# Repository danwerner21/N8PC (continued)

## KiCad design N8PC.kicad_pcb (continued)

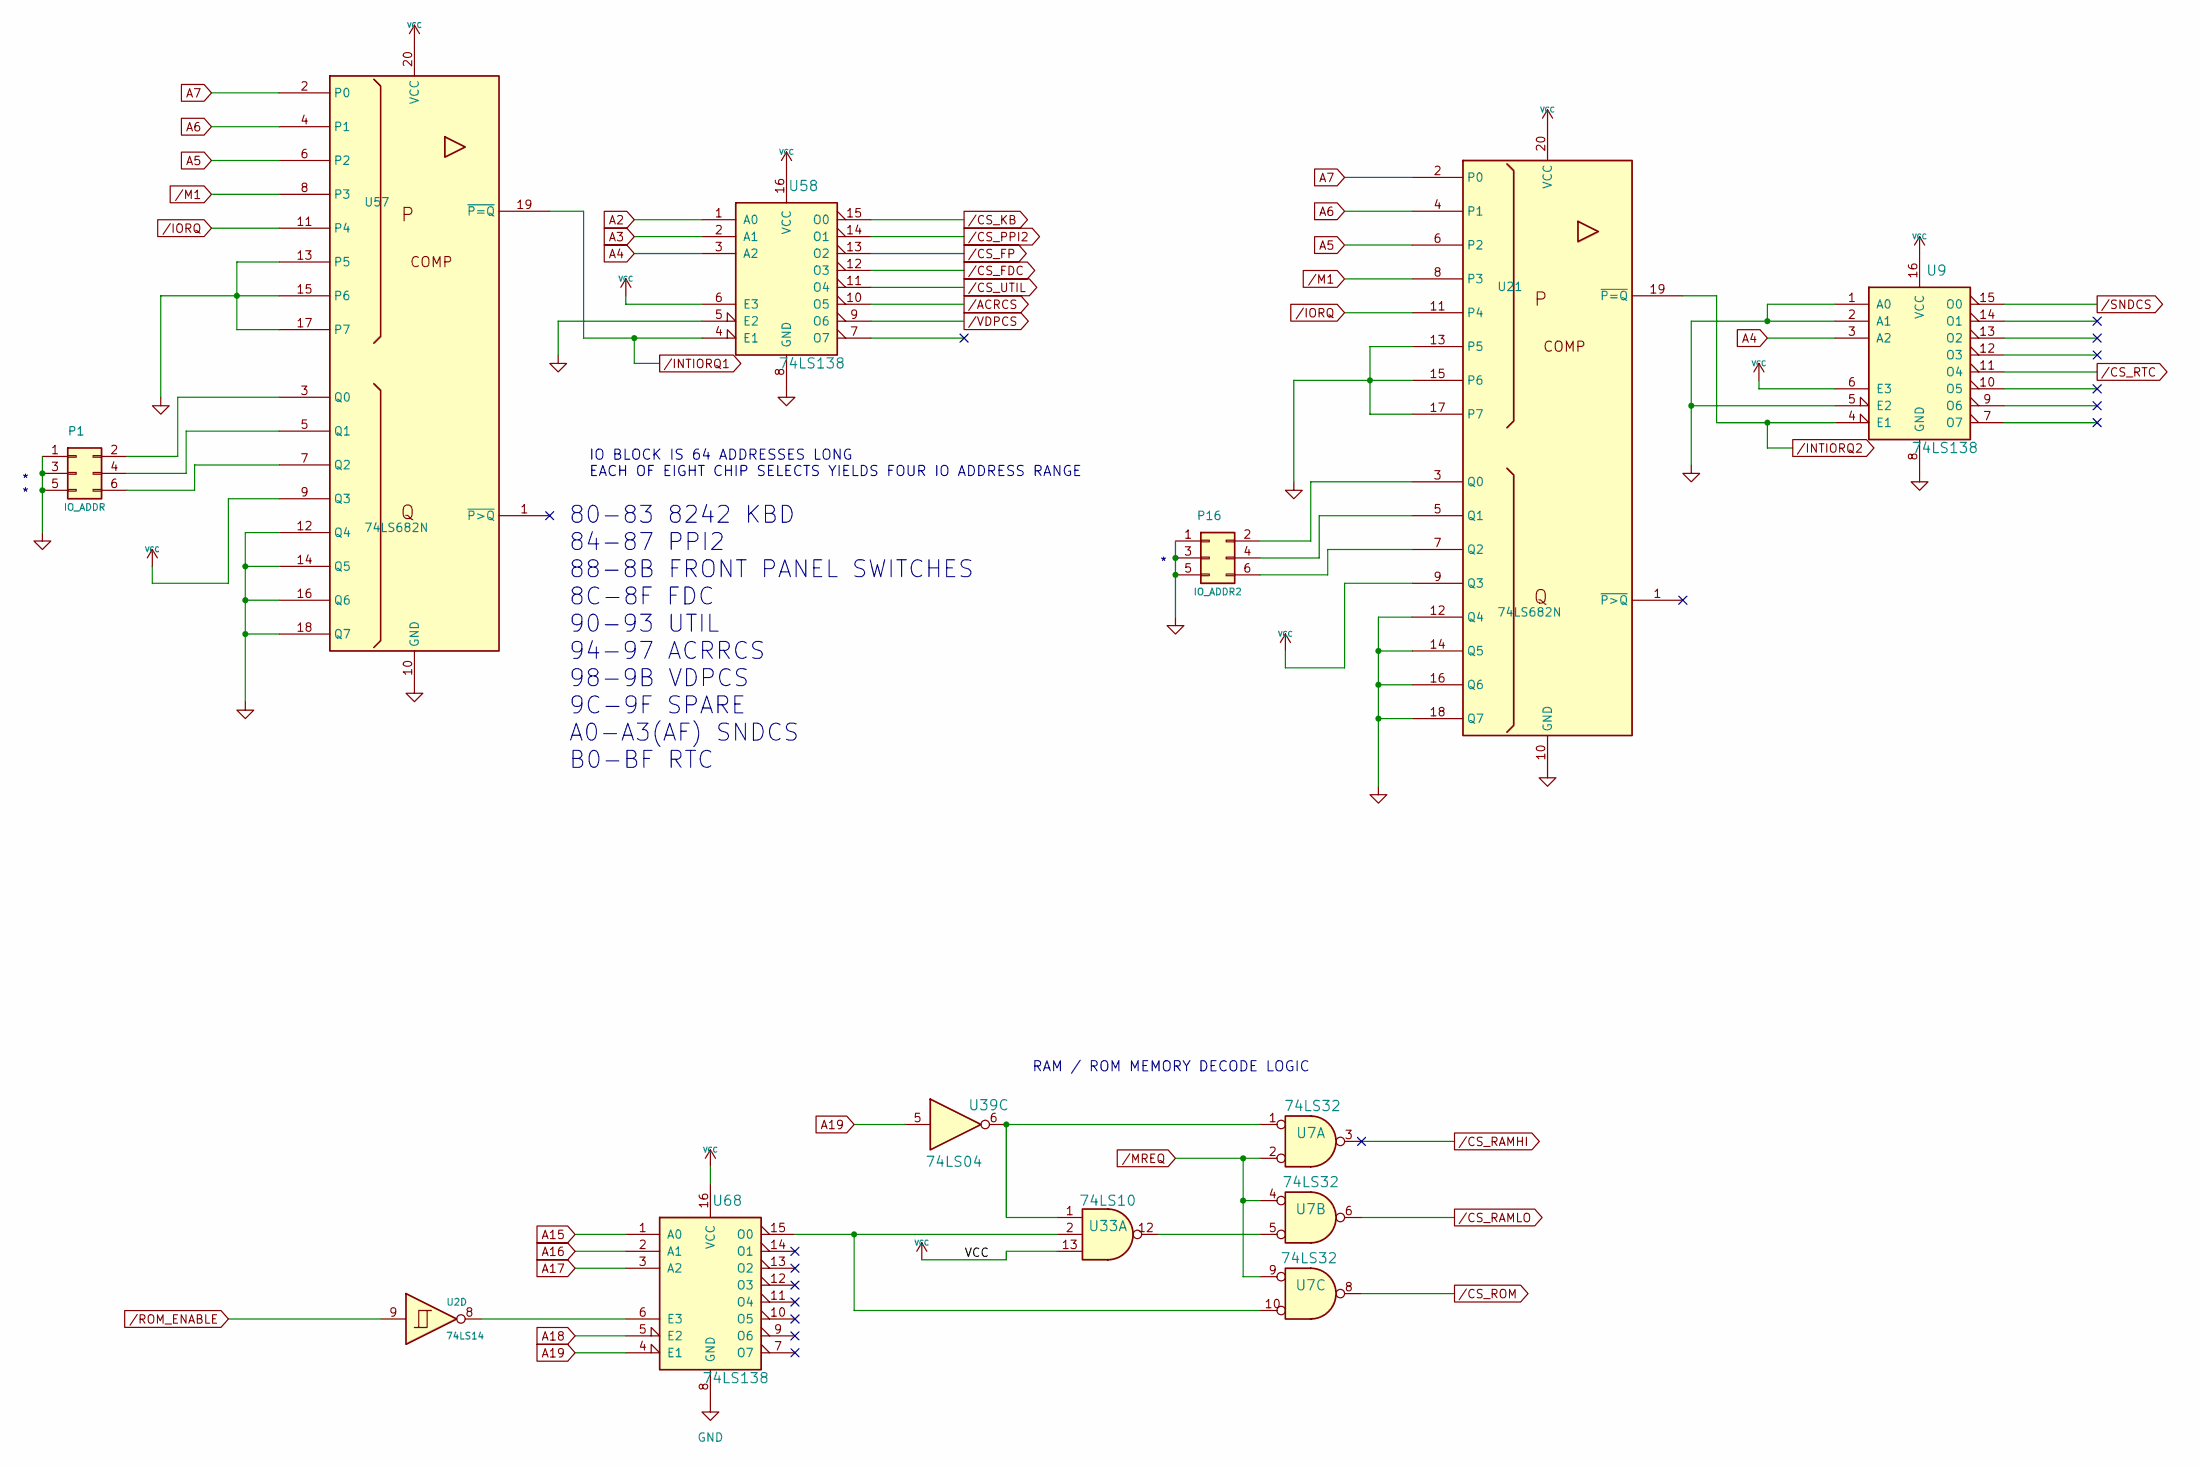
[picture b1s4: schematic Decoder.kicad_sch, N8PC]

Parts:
P1: IO_ADDR; STD_DDW_PinHeader_2x03
P16: IO_ADDR2; STD_DDW_PinHeader_2x03
U2: 74LS14; STD_DDW_DIP14
U7: 74LS32; STD_DDW_DIP14
U9, U58, U68: 74LS138; STD_DDW_DIP16
U21, U57: 74LS682N; STD_DDW_DIP20
U33: 74LS10; STD_DDW_DIP14
U39: 74LS04; STD_DDW_DIP14

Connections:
+5V: U9.6 (E3), U9.16 (VCC), U21.9 (Q3), U21.20 (VCC), U33.13, U57.9 (Q3), U57.20 (VCC), U58.6 (E3), U58.16 (VCC), U68.16 (VCC); also elsewhere on the board
A2: U58.1 (A0); also elsewhere on the board
A3: U58.2 (A1); also elsewhere on the board
A4: U9.3 (A2), U58.3 (A2); also elsewhere on the board
A5: U21.6 (P2), U57.6 (P2); also elsewhere on the board
A6: U21.4 (P1), U57.4 (P1); also elsewhere on the board
A7: U21.2 (P0), U57.2 (P0); also elsewhere on the board
A15: U68.1 (A0); also elsewhere on the board
A16: U68.2 (A1); also elsewhere on the board
A17: U68.3 (A2); also elsewhere on the board
A18: U68.5 (E2); also elsewhere on the board
A19: U39.5, U68.4 (E1); also elsewhere on the board
GND: P1.1, P1.3, P1.5, P16.1, P16.3, P16.5, U9.1 (A0), U9.2 (A1), U9.5 (E2), U9.8 (GND), U21.10 (GND), U21.12 (Q4), U21.13 (P5), U21.14 (Q5), U21.15 (P6), U21.16 (Q6), U21.17 (P7), U21.18 (Q7), U57.10 (GND), U57.12 (Q4), U57.13 (P5), U57.14 (Q5), U57.15 (P6), U57.16 (Q6), U57.17 (P7), U57.18 (Q7), U58.5 (E2), U58.8 (GND), U68.8 (GND); also elsewhere on the board
unnamed: P1.2, U57.3 (Q0)
unnamed: P1.4, U57.5 (Q1)
unnamed: P1.6, U57.7 (Q2)
unnamed: P16.2, U21.3 (Q0)
unnamed: P16.4, U21.5 (Q1)
unnamed: P16.6, U21.7 (Q2)
unnamed: U7.1, U33.1, U39.6
unnamed: U7.5, U33.12
unnamed: U2.8, U68.6 (E3)
unnamed: U7.10, U33.2, U68.15 (O0)
/ACRCS: U58.10 (O5); also elsewhere on the board
/CS_FDC: U58.12 (O3); also elsewhere on the board
/CS_FP: U58.13 (O2); also elsewhere on the board
/CS_KB: U58.15 (O0); also elsewhere on the board
/CS_PPI2: U58.14 (O1); also elsewhere on the board
/CS_RAMHI: U7.3
/CS_RAMLO: U7.6; also elsewhere on the board
/CS_ROM: U7.8; also elsewhere on the board
/CS_RTC: U9.11 (O4); also elsewhere on the board
/CS_UTIL: U58.11 (O4); also elsewhere on the board
/INTIORQ1: U57.19 (~P=Q), U58.4 (E1); also elsewhere on the board
/INTIORQ2: U9.4 (E1), U21.19 (~P=Q); also elsewhere on the board
/IORQ: U21.11 (P4), U57.11 (P4); also elsewhere on the board
/M1: U21.8 (P3), U57.8 (P3); also elsewhere on the board
/MREQ: U7.2, U7.4, U7.9; also elsewhere on the board
/ROM_ENABLE: U2.9; also elsewhere on the board
/SNDCS: U9.15 (O0); also elsewhere on the board
/VDPCS: U58.9 (O6); also elsewhere on the board

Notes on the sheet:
* *
RAM / ROM MEMORY DECODE LOGIC
80-83 8242 KBD 84-87 PPI2 88-8B FRONT PANEL SWITCHES 8C-8F FDC 90-93 UTIL 94-97 ACRRCS 98-9B VDPCS 9C-9F SPARE A0-A3(AF) SNDCS B0-BF RTC
IO BLOCK IS 64 ADDRESSES LONG EACH OF EIGHT CHIP SELECTS YIELDS FOUR IO ADDRESS RANGE

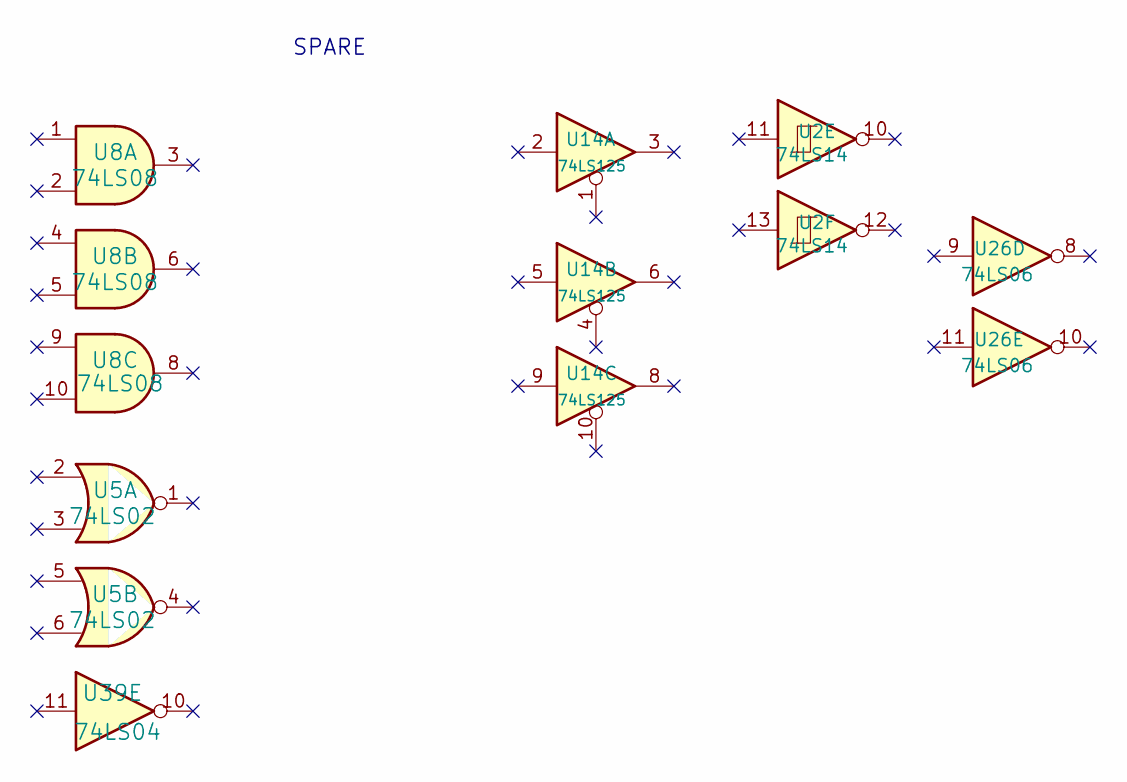
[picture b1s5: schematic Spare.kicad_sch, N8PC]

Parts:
U2: 74LS14; STD_DDW_DIP14
U5: 74LS02; STD_DDW_DIP14
U8: 74LS08; STD_DDW_DIP14
U14: 74LS125; STD_DDW_DIP14
U26: 74LS06; STD_DDW_DIP14
U39: 74LS04; STD_DDW_DIP14

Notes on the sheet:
SPARE

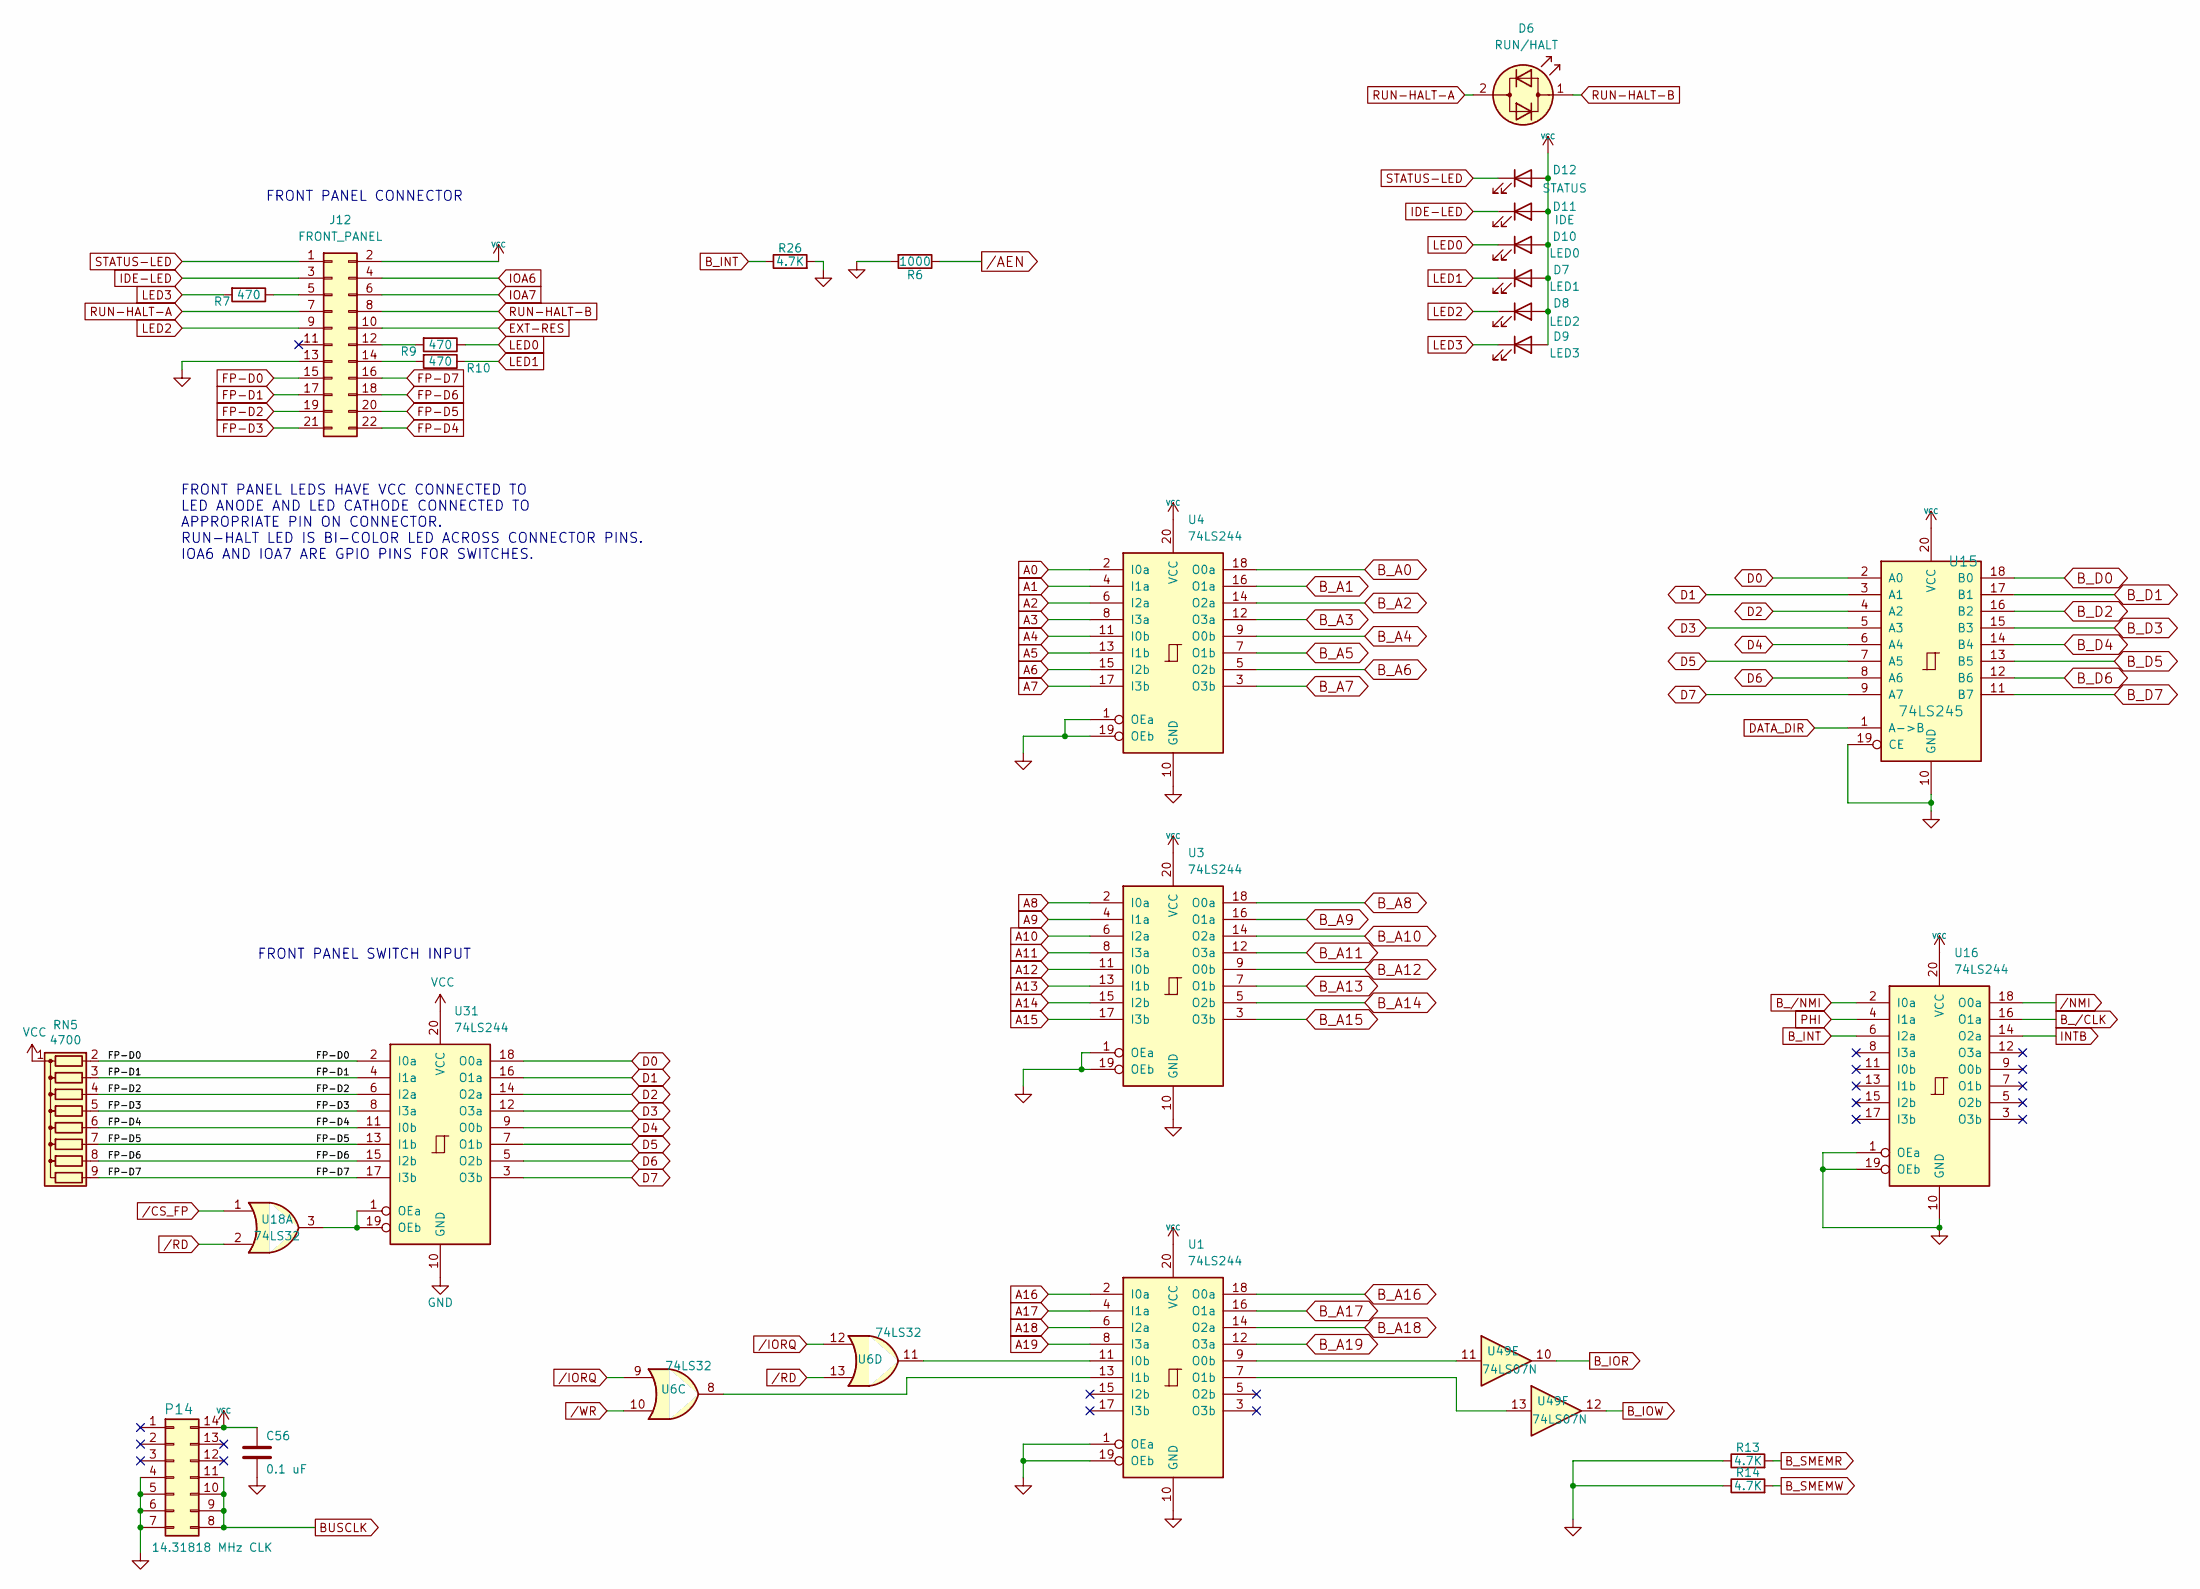
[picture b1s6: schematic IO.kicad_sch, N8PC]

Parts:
C56: 0.1 uF; STD_DDW_CAP
D6: RUN/HALT; STD_DDW_LED5
D7: LED1; STD_DDW_LED5
D8: LED2; STD_DDW_LED5
D9: LED3; STD_DDW_LED5
D10: LED0; STD_DDW_LED5
D11: IDE; STD_DDW_LED5
D12: STATUS; STD_DDW_LED5
J12: FRONT_PANEL; STD_DDW_PinHeader_2x11
P14: 14.31818 MHz CLK; STD_DDW_DIP14
R6: 1000; STD_DDW_RESISTOR
R7, R9, R10: 470; STD_DDW_RESISTOR
R13, R14, R26: 4.7K; STD_DDW_RESISTOR
RN5: 4700; R_Array_SIP9
U1, U3, U4, U16, U31: 74LS244; STD_DDW_DIP20
U6, U18: 74LS32; STD_DDW_DIP14
U15: 74LS245; STD_DDW_DIP20
U49: 74LS07N; STD_DDW_DIP14

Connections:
+5V: C56.1, D7.2 (A), D8.2 (A), D9.2 (A), D10.2 (A), D11.2 (A), D12.2 (A), J12.2, P14.14, RN5.1 (common), U1.20 (VCC), U3.20 (VCC), U4.20 (VCC), U15.20 (VCC), U16.20 (VCC), U31.20 (VCC); also elsewhere on the board
A0: U4.2 (I0a); also elsewhere on the board
A1: U4.4 (I1a); also elsewhere on the board
A2: U4.6 (I2a); also elsewhere on the board
A3: U4.8 (I3a); also elsewhere on the board
A4: U4.11 (I0b); also elsewhere on the board
A5: U4.13 (I1b); also elsewhere on the board
A6: U4.15 (I2b); also elsewhere on the board
A7: U4.17 (I3b); also elsewhere on the board
A8: U3.2 (I0a); also elsewhere on the board
A9: U3.4 (I1a); also elsewhere on the board
A10: U3.6 (I2a); also elsewhere on the board
A11: U3.8 (I3a); also elsewhere on the board
A12: U3.11 (I0b); also elsewhere on the board
A13: U3.13 (I1b); also elsewhere on the board
A14: U3.15 (I2b); also elsewhere on the board
A15: U3.17 (I3b); also elsewhere on the board
A16: U1.2 (I0a); also elsewhere on the board
A17: U1.4 (I1a); also elsewhere on the board
A18: U1.6 (I2a); also elsewhere on the board
A19: U1.8 (I3a); also elsewhere on the board
BUSCLK: P14.8, P14.9, P14.10, P14.11; also elsewhere on the board
B_A0: U4.18 (O0a); also elsewhere on the board
B_A1: U4.16 (O1a); also elsewhere on the board
B_A2: U4.14 (O2a); also elsewhere on the board
B_A3: U4.12 (O3a); also elsewhere on the board
B_A4: U4.9 (O0b); also elsewhere on the board
B_A5: U4.7 (O1b); also elsewhere on the board
B_A6: U4.5 (O2b); also elsewhere on the board
B_A7: U4.3 (O3b); also elsewhere on the board
B_A8: U3.18 (O0a); also elsewhere on the board
B_A9: U3.16 (O1a); also elsewhere on the board
B_A10: U3.14 (O2a); also elsewhere on the board
B_A11: U3.12 (O3a); also elsewhere on the board
B_A12: U3.9 (O0b); also elsewhere on the board
B_A13: U3.7 (O1b); also elsewhere on the board
B_A14: U3.5 (O2b); also elsewhere on the board
B_A15: U3.3 (O3b); also elsewhere on the board
B_A16: U1.18 (O0a); also elsewhere on the board
B_A17: U1.16 (O1a); also elsewhere on the board
B_A18: U1.14 (O2a); also elsewhere on the board
B_A19: U1.12 (O3a); also elsewhere on the board
B_D0: U15.18 (B0); also elsewhere on the board
B_D1: U15.17 (B1); also elsewhere on the board
B_D2: U15.16 (B2); also elsewhere on the board
B_D3: U15.15 (B3); also elsewhere on the board
B_D4: U15.14 (B4); also elsewhere on the board
B_D5: U15.13 (B5); also elsewhere on the board
B_D6: U15.12 (B6); also elsewhere on the board
B_D7: U15.11 (B7); also elsewhere on the board
B_INT: R26.1, U16.6 (I2a); also elsewhere on the board
B_IOR: U49.10; also elsewhere on the board
B_IOW: U49.12; also elsewhere on the board
B_SMEMR: R13.2; also elsewhere on the board
B_SMEMW: R14.2; also elsewhere on the board
B_/CLK: U16.16 (O1a); also elsewhere on the board
B_/NMI: U16.2 (I0a); also elsewhere on the board
D0: U15.2 (A0), U31.18 (O0a); also elsewhere on the board
D1: U15.3 (A1), U31.16 (O1a); also elsewhere on the board
D2: U15.4 (A2), U31.14 (O2a); also elsewhere on the board
D3: U15.5 (A3), U31.12 (O3a); also elsewhere on the board
D4: U15.6 (A4), U31.9 (O0b); also elsewhere on the board
D5: U15.7 (A5), U31.7 (O1b); also elsewhere on the board
D6: U15.8 (A6), U31.5 (O2b); also elsewhere on the board
D7: U15.9 (A7), U31.3 (O3b); also elsewhere on the board
DATA_DIR: U15.1 (A->B); also elsewhere on the board
EXT-RES: J12.10; also elsewhere on the board
FP-D0: J12.15, RN5.2 (R1), U31.2 (I0a)
FP-D1: J12.17, RN5.3 (R2), U31.4 (I1a)
FP-D2: J12.19, RN5.4 (R3), U31.6 (I2a)
FP-D3: J12.21, RN5.5 (R4), U31.8 (I3a)
FP-D4: J12.22, RN5.6 (R5), U31.11 (I0b)
FP-D5: J12.20, RN5.7 (R6), U31.13 (I1b)
FP-D6: J12.18, RN5.8 (R7), U31.15 (I2b)
FP-D7: J12.16, RN5.9 (R8), U31.17 (I3b)
GND: C56.2, J12.13, P14.4, P14.5, P14.6, P14.7, R6.2, R13.1, R14.1, R26.2, U1.1 (OEa), U1.10 (GND), U1.19 (OEb), U3.1 (OEa), U3.10 (GND), U3.19 (OEb), U4.1 (OEa), U4.10 (GND), U4.19 (OEb), U15.10 (GND), U15.19 (CE), U16.1 (OEa), U16.10 (GND), U16.19 (OEb), U31.10 (GND); also elsewhere on the board
IDE-LED: D11.1 (K), J12.3; also elsewhere on the board
INTB: U16.14 (O2a); also elsewhere on the board
IOA6: J12.4; also elsewhere on the board
IOA7: J12.6; also elsewhere on the board
LED0: D10.1 (K), R9.1; also elsewhere on the board
LED1: D7.1 (K), R10.1; also elsewhere on the board
LED2: D8.1 (K), J12.9; also elsewhere on the board
LED3: D9.1 (K), R7.2; also elsewhere on the board
unnamed: J12.5, R7.1
unnamed: J12.12, R9.2
unnamed: J12.14, R10.2
unnamed: U1.11 (I0b), U6.11
unnamed: U1.13 (I1b), U6.8
unnamed: U1.9 (O0b), U49.11
unnamed: U1.7 (O1b), U49.13
unnamed: U18.3, U31.1 (OEa), U31.19 (OEb)
PHI: U16.4 (I1a); also elsewhere on the board
RUN-HALT-A: D6.2 (AK), J12.7; also elsewhere on the board
RUN-HALT-B: D6.1 (KA), J12.8; also elsewhere on the board
STATUS-LED: D12.1 (K), J12.1; also elsewhere on the board
/AEN: R6.1; also elsewhere on the board
/CS_FP: U18.1; also elsewhere on the board
/IORQ: U6.9, U6.12; also elsewhere on the board
/NMI: U16.18 (O0a); also elsewhere on the board
/RD: U6.13, U18.2; also elsewhere on the board
/WR: U6.10; also elsewhere on the board

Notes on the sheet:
FRONT PANEL CONNECTOR
FRONT PANEL LEDS HAVE VCC CONNECTED TO LED ANODE AND LED CATHODE CONNECTED TO APPROPRIATE PIN ON CONNECTOR. RUN-HALT LED IS BI-COLOR LED ACROSS CONNECTOR PINS. IOA6 AND IOA7 ARE GPIO PINS FOR SWITCHES.
FRONT PANEL SWITCH INPUT

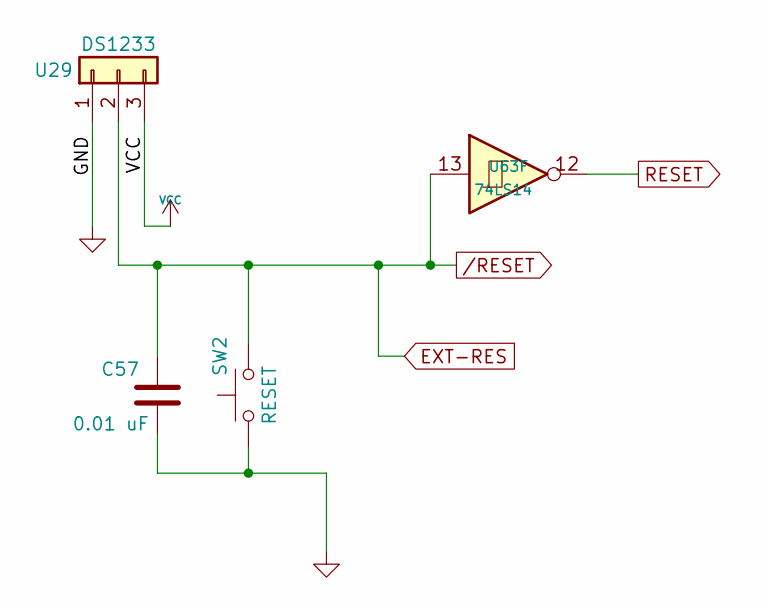
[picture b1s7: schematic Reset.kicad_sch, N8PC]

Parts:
C57: 0.01 uF; STD_DDW_CAP
SW2: RESET; STD_DDW_TACTSW
U29: DS1233; STD_DDW_TO92
U63: 74LS14; STD_DDW_DIP14

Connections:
+5V: U29.3; also elsewhere on the board
EXT-RES: C57.1, SW2.2, U29.2, U63.13; also elsewhere on the board
GND: C57.2, SW2.1, U29.1; also elsewhere on the board
RESET: U63.12; also elsewhere on the board

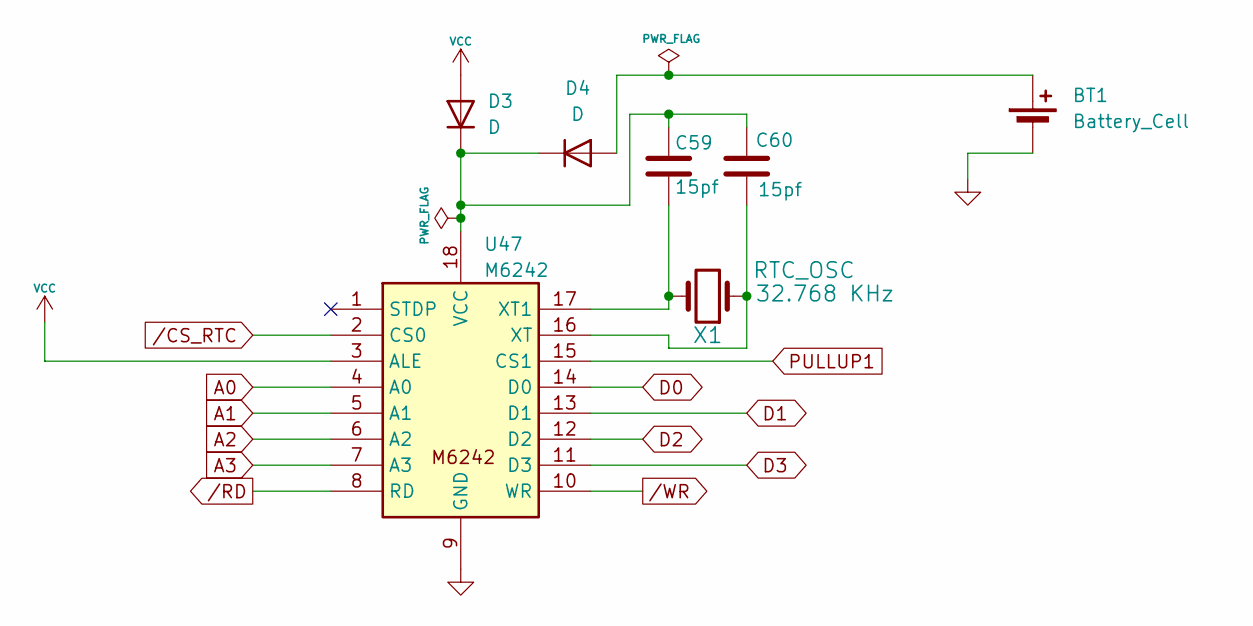
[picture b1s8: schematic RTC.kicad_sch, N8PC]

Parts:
BT1: Battery_Cell; BatteryHolder_MYOUNG_BS-07-A1BJ001_CR2032
C59, C60: 15pf; STD_DDW_CAP
D3, D4: D; STD_DDW_DIODE
U47: M6242; STD_DDW_DIP18
X1: RTC_OSC; DDW_STD_RTCCRYSTAL

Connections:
+5V: D3.2 (A), U47.3 (ALE); also elsewhere on the board
A0: U47.4 (A0); also elsewhere on the board
A1: U47.5 (A1); also elsewhere on the board
A2: U47.6 (A2); also elsewhere on the board
A3: U47.7 (A3); also elsewhere on the board
D0: U47.14 (D0); also elsewhere on the board
D1: U47.13 (D1); also elsewhere on the board
D2: U47.12 (D2); also elsewhere on the board
D3: U47.11 (D3); also elsewhere on the board
GND: BT1.2 (-), U47.9 (GND); also elsewhere on the board
unnamed: BT1.1 (+), D4.2 (A)
unnamed: C59.1, C60.1, D3.1 (K), D4.1 (K), U47.18 (VCC)
unnamed: C59.2, U47.17 (XT1), X1.2
unnamed: C60.2, U47.16 (XT), X1.1
PULLUP1: U47.15 (CS1); also elsewhere on the board
/CS_RTC: U47.2 (CS0); also elsewhere on the board
/RD: U47.8 (RD); also elsewhere on the board
/WR: U47.10 (WR); also elsewhere on the board

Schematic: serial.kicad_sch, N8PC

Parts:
C55, C58, C61, C62, C63, C64, C67, C71, C72, C73: 1.0 uF; STD_DDW_PCAP
J17, J19: TTL SERIAL CONSOLE; STD_DDW_PINHEAD_V_1x06
J18, J20: TTL CONSOLE PWR; STD_DDW_PINHEAD_V_1x02
JP2: CTS0; STD_DDW_PINHEAD_V_1x02
JP3: CTS1; STD_DDW_PINHEAD_V_1x02
P13, P18: SERIAL; STD_DDW_PINHEAD_V_2x05
R4: 4.7K; STD_DDW_RESISTOR
U10, U35: MAX232; STD_DDW_DIP16

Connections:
+5V: C61.1, C63.2, C71.2, C72.1, J18.1, J20.1, R4.1, U10.16 (VCC), U35.16 (VCC); also elsewhere on the board
CTS0: JP2.2 (B), P18.6, U35.13 (R1IN)
CTS1: JP3.2 (B), P13.6, U10.13 (R1IN)
CTS_TTL0: J17.6, U35.12 (R1OUT); also elsewhere on the board
CTS_TTL1: J19.6, U10.12 (R1OUT); also elsewhere on the board
GND: C61.2, C64.1, C72.2, C73.1, J17.1, J19.1, P13.9, P18.9, U10.15 (GND), U35.15 (GND); also elsewhere on the board
unnamed: J17.3, J18.2
unnamed: J19.3, J20.2
unnamed: JP2.1 (A), JP3.1 (A), R4.2
unnamed: C58.1, U10.1 (C1+)
unnamed: C58.2, U10.3 (C1-)
unnamed: C62.1, U10.4 (C2+)
unnamed: C62.2, U10.5 (C2-)
unnamed: C63.1, U10.2 (VS+)
unnamed: C64.2, U10.6 (VS-)
unnamed: C55.1, U35.1 (C1+)
unnamed: C55.2, U35.3 (C1-)
unnamed: C67.1, U35.4 (C2+)
unnamed: C67.2, U35.5 (C2-)
unnamed: C71.1, U35.2 (VS+)
unnamed: C73.2, U35.6 (VS-)
RTS0: P18.4, U35.14 (T1OUT)
RTS1: P13.4, U10.14 (T1OUT)
RTS_TTL0: J17.2, U35.11 (T1IN); also elsewhere on the board
RTS_TTL1: J19.2, U10.11 (T1IN); also elsewhere on the board
RX0: P18.3, U35.8 (R2IN)
RX1: P13.3, U10.8 (R2IN)
SIN_TTL0: J17.4, U35.9 (R2OUT); also elsewhere on the board
SIN_TTL1: J19.4, U10.9 (R2OUT); also elsewhere on the board
SOUT_TTL0: J17.5, U35.10 (T2IN); also elsewhere on the board
SOUT_TTL1: J19.5, U10.10 (T2IN); also elsewhere on the board
TX0: P18.5, U35.7 (T2OUT)
TX1: P13.5, U10.7 (T2OUT)

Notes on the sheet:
CTS is an inverted signal on the RS-232 port. So it is really /CTS. To assert the signal, it must be tied to SPACE, which is a + RS-232 voltage. (MARK, or true, is a - RS-232 voltage.)

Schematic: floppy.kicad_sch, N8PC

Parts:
P27: FLOPPY; STD_DDW_PinHeader_2x17
P41: OSC_FDC; STD_DDW_DIP14
R46, R47: 4700; STD_DDW_RESISTOR
RP1: 150; STD_DDW_SIP9
U6: 74LS32; STD_DDW_DIP14
U8: 74LS08; STD_DDW_DIP14
U32: 74LS139; STD_DDW_DIP16
U33: 74LS10; STD_DDW_DIP14
U39: 74LS04; STD_DDW_DIP14
U61: WD37C65BJM; STD_DDW_PLCC-44

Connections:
+5V: P41.14, RP1.1 (common), U61.44 (VCC); also elsewhere on the board
A0: U32.2 (A0), U61.4 (A0); also elsewhere on the board
A1: U6.5, U32.3 (A1), U39.1; also elsewhere on the board
D0: U61.7 (DB0); also elsewhere on the board
D1: U61.8 (DB1); also elsewhere on the board
D2: U61.9 (DB2); also elsewhere on the board
D3: U61.10 (DB3); also elsewhere on the board
D4: U61.11 (DB4); also elsewhere on the board
D5: U61.12 (DB5); also elsewhere on the board
D6: U61.13 (DB6); also elsewhere on the board
D7: U61.14 (DB7); also elsewhere on the board
GND: P27.1, P27.3, P27.5, P27.7, P27.9, P27.11, P27.13, P27.15, P27.17, P27.19, P27.21, P27.23, P27.25, P27.27, P27.29, P27.31, P27.33, P41.4, P41.5, P41.6, P41.7, R46.1, R47.1, U61.17 (/DCHGEN), U61.23 (XT2), U61.24 (DRV), U61.34 (GND); also elsewhere on the board
unnamed: P27.2, U61.39 (/RWC/RPM)
unnamed: P27.8, RP1.7 (R6), U61.43 (/IDX)
unnamed: P27.10, U61.37 (/MO2/DS4)
unnamed: P27.12, U61.33 (/DS1)
unnamed: P27.14, U61.35 (/DS2)
unnamed: P27.6, P27.16, U61.36 (/MO1/DS3)
unnamed: P27.18, U61.31 (/DIRC)
unnamed: P27.20, U61.32 (/STEP)
unnamed: P27.22, U61.30 (/WD)
unnamed: P27.24, U61.29 (/WE)
unnamed: P27.26, RP1.6 (R5), U61.42 (/TR00)
unnamed: P27.28, RP1.5 (R4), U61.41 (/WP)
unnamed: P27.30, RP1.3 (R2), U61.21 (/RDD)
unnamed: P27.32, U61.28 (/HS)
unnamed: P27.34, RP1.4 (R3), U61.40 (/DCHG)
unnamed: RP1.8 (R7), U61.27 (PCVAL)
unnamed: U32.5 (O1), U61.19 (/LDCR)
unnamed: U32.6 (O2), U61.18 (/LDOR)
unnamed: U6.2, U39.2
unnamed: R47.2, U39.9, U61.15 (DMA)
unnamed: R46.2, U39.13, U61.16 (IRQ)
unnamed: U33.8, U61.6 (TC)
unnamed: P41.8, P41.9, P41.10, P41.11, U61.26 (XT1)
unnamed: U6.6, U61.3 (/CS)
unnamed: U8.11, U61.5 (/DACK)
RESET: U61.20 (RST); also elsewhere on the board
/CS_FDC: U6.1, U6.4; also elsewhere on the board
/CS_UTIL: U32.1 (E); also elsewhere on the board
/DACK1: U8.12, U32.4 (O0)
/DACK_AND_TC: U8.13, U32.7 (O3), U33.10
/DREQ1: U39.8; also elsewhere on the board
/INT_FDC: U39.12; also elsewhere on the board
/RD: U61.1 (/RD); also elsewhere on the board
/TC: U6.3, U33.9
/TEND1: U33.11; also elsewhere on the board
/WR: U61.2 (/WR); also elsewhere on the board

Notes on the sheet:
IBM floppy connector A: = DS1 (no twist) B: = DS2 (twist)
CS_FDC IS IO BASE + 12 CS_UTIL IS IO BASE + 16 0 IS /DACK 1 IS /LDCR 2 IS /LDOR 3 IS /DACK AND TC
key

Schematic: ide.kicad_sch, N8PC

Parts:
K2: IDE_PWR; STD_DDW_PINHEAD_V_1x03
P29: PPIDE; STD_DDW_PINHEAD_V_2x20
P31: PARALLEL EXP; STD_DDW_PINHEAD_V_2x13
R36: 470; STD_DDW_RESISTOR
U38: 8255; STD_DDW_DIP40
U63: 74LS14; STD_DDW_DIP14

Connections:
+5V: K2.3, U38.26 (VCC); also elsewhere on the board
A0: U38.9 (A0); also elsewhere on the board
A1: U38.8 (A1); also elsewhere on the board
D0: U38.34 (D0); also elsewhere on the board
D1: U38.33 (D1); also elsewhere on the board
D2: U38.32 (D2); also elsewhere on the board
D3: U38.31 (D3); also elsewhere on the board
D4: U38.30 (D4); also elsewhere on the board
D5: U38.29 (D5); also elsewhere on the board
D6: U38.28 (D6); also elsewhere on the board
D7: U38.27 (D7); also elsewhere on the board
GND: K2.1, P29.2, P29.19, P29.22, P29.24, P29.26, P29.30, P29.40, P31.26, U38.7 (GND); also elsewhere on the board
IDE-LED: R36.2; also elsewhere on the board
unnamed: K2.2, P29.20, P31.25
unnamed: P29.39, R36.1
PA0: P29.17, P31.2, U38.4 (PA0)
PA1: P29.15, P31.4, U38.3 (PA1)
PA2: P29.13, P31.6, U38.2 (PA2)
PA3: P29.11, P31.8, U38.1 (PA3)
PA4: P29.9, P31.10, U38.40 (PA4)
PA5: P29.7, P31.12, U38.39 (PA5)
PA6: P29.5, P31.14, U38.38 (PA6)
PA7: P29.3, P31.16, U38.37 (PA7)
PB0: P29.4, P31.18, U38.18 (PB0)
PB1: P29.6, P31.20, U38.19 (PB1)
PB2: P29.8, P31.22, U38.20 (PB2)
PB3: P29.10, P31.24, U38.21 (PB3)
PB4: P29.12, P31.23, U38.22 (PB4)
PB5: P29.14, P31.21, U38.23 (PB5)
PB6: P29.16, P31.19, U38.24 (PB6)
PB7: P29.18, P31.17, U38.25 (PB7)
PC0: P29.35, P31.1, U38.14 (PC0)
PC1: P29.33, P31.3, U38.15 (PC1)
PC2: P29.36, P31.5, U38.16 (PC2)
PC3: P31.7, U38.17 (PC3), U63.9
PC4: P31.9, U38.13 (PC4), U63.11
PC5: P31.11, U38.12 (PC5), U63.3
PC6: P31.13, U38.11 (PC6), U63.5
PC7: P31.15, U38.10 (PC7), U63.1
RESET: U38.35 (RESET); also elsewhere on the board
/CS_PPI2: U38.6 (~CS); also elsewhere on the board
/PC3: P29.37, U63.8
/PC4: P29.38, U63.10
/PC5: P29.23, U63.4
/PC6: P29.25, U63.6
/PC7: P29.1, U63.2
/RD: U38.5 (~RD); also elsewhere on the board
/WR: U38.36 (~WR); also elsewhere on the board

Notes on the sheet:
NOTE: EITHER PPIDE OR PARALLEL EXPANSION PORT CAN BE USED BUT NOT BOTH SIMULTANEOUSLY.
K2 = USE FOR VCC OR GND PIN 25 PARALLEL PORT

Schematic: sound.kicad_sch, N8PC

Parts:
C101, C102: 270 pF; STD_DDW_PCAP
C109, C110: 10 uF; STD_DDW_PCAP
JP10: JUMPER; STD_DDW_PINHEAD_V_1x02
P15: AUDIO; STD_DDW_PINHEAD_V_2x05
P43: CHAN_MIX; STD_DDW_PinHeader_2x02
P51: JOYSTICK0; STD_DDW_PINHEAD_V_2x05
P52: JOYSTICK1; STD_DDW_PINHEAD_V_2x05
R16, R22, R23, R24: 10K; STD_DDW_RESISTOR
R17, R19, R21: 1000; STD_DDW_RESISTOR
RR8: 4700; STD_DDW_SIP10
RV1, RV2: 4700; STD_DDW_Potentiometer
U5: 74LS02; STD_DDW_DIP14
U34: 74LS393; STD_DDW_DIP14
U48: AY-3-8910; STD_DDW_DIP40
U49: 74LS07N; STD_DDW_DIP14
U51: STEREO_JACK; STD_DDW_Jack_3.5mm
U66, U67: 74LS157; STD_DDW_DIP16

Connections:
+5V: P15.1, P15.2, P51.9, P52.9, RR8.1 (common), U48.25 (A8), U48.28 (BC2), U48.40 (VCC), U66.16 (VCC), U67.16 (VCC); also elsewhere on the board
A0: U5.12; also elsewhere on the board
ACR5: P15.8; also elsewhere on the board
D0: U48.37 (D0); also elsewhere on the board
D1: U48.36 (D1); also elsewhere on the board
D2: U48.35 (D2); also elsewhere on the board
D3: U48.34 (D3); also elsewhere on the board
D4: U48.33 (D4); also elsewhere on the board
D5: U48.32 (D5); also elsewhere on the board
D6: U48.31 (D6); also elsewhere on the board
D7: U48.30 (D7); also elsewhere on the board
GND: C101.1, C102.2, JP10.1 (A), P15.10, P51.8, P52.8, R17.2, R19.2, R21.2, RV1.1, RV1.2, RV2.3, U48.1 (GND), U48.24 (A9), U51.S, U66.8 (GND), U66.15 (E), U67.8 (GND), U67.15 (E); also elsewhere on the board
IOA0: U48.21 (IOA0), U66.4 (Za)
IOA1: U48.20 (IOA1), U66.7 (Zb)
IOA2: U48.19 (IOA2), U66.12 (Zd)
IOA3: U48.18 (IOA3), U66.9 (Zc)
IOA4: U48.17 (IOA4), U67.4 (Za)
IOA5: U48.16 (IOA5), U67.7 (Zb)
IOA6: U48.15 (IOA6); also elsewhere on the board
IOA7: P15.4, U48.14 (IOA7); also elsewhere on the board
IOB0: U48.13 (IOB0), U49.1
IOB1: U48.12 (IOB1), U49.3
IOB2: U48.11 (IOB2), U49.5
IOB3: U48.10 (IOB3), U49.9
IOB4: P51.6, U48.9 (IOB4)
IOB5: P52.6, U48.8 (IOB5)
IOB6: U48.7 (IOB6), U66.1 (S), U67.1 (S)
IOB7: P15.6, U48.6 (IOB7)
unnamed: C101.2, C109.1, R22.1, R24.2, RV1.3
unnamed: C102.1, C110.1, R16.2, R23.1, RV2.1, RV2.2
unnamed: JP10.2 (B), U48.26 (TEST2)
unnamed: C109.2, P15.3, U51.T
unnamed: C110.2, P15.9, U51.R
unnamed: P43.1, R19.1, R23.2, U48.38 (OUTC)
unnamed: P43.2, P43.4, R16.1, R17.1, R24.1, U48.3 (OUTB)
unnamed: P43.3, R21.1, R22.2, U48.4 (OUTA)
unnamed: U34.3 (Q0), U48.22 (CLOCK)
unnamed: U5.13, U48.29 (BC1)
unnamed: U5.10, U48.27 (BDIR)
RESET: U34.2 (MR); also elsewhere on the board
VRY: U34.1 (CP); also elsewhere on the board
/BCK-A: P51.3, RR8.3 (R2), U66.5 (I0b)
/BCK-B: P52.3, RR8.8 (R7), U66.6 (I1b)
/FWD-A: P51.1, RR8.2 (R1), U66.2 (I0a)
/FWD-B: P52.1, RR8.7 (R6), U66.3 (I1a)
/LFT-A: P51.5, RR8.4 (R3), U66.14 (I0d)
/LFT-B: P52.5, RR8.9 (R8), U66.13 (I1d)
/RESAY3: U48.23 (RESET); also elsewhere on the board
/RGT-A: P51.7, RR8.5 (R4), U66.11 (I0c)
/RGT-B: P52.7, RR8.10 (R9), U66.10 (I1c)
/SNDCS: U5.9, U5.11; also elsewhere on the board
/TRG1-A: P51.2, U49.2, U67.2 (I0a); also elsewhere on the board
/TRG1-B: P52.2, U49.4, U67.3 (I1a); also elsewhere on the board
/TRG2-A: P51.4, U49.6, U67.5 (I0b); also elsewhere on the board
/TRG2-B: P52.4, U49.8, U67.6 (I1b); also elsewhere on the board
/WR: U5.8; also elsewhere on the board

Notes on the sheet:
NOTE: JP10 SHOULD BE LEFT OPEN

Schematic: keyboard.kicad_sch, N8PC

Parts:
J15: MOUSE; PS2_DIN
J16: KEYBOARD; PS2_DIN
NT1: NetTie_2; NetTie-2_THT_Pad0.3mm
U18: 74LS32; STD_DDW_DIP14
U24: CLK; STD_DDW_DIP14
U25: 82c42; STD_DDW_DIP40
U26: 74LS06; STD_DDW_DIP14

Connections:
+5V: J15.4, J16.4, U24.1, U24.14, U25.5 (SS), U25.40 (VCC); also elsewhere on the board
A0: U25.9 (A0); also elsewhere on the board
CLK: U24.8, U24.11, U25.3 (X2)
D0: U25.12 (D0); also elsewhere on the board
D1: U25.13 (D1); also elsewhere on the board
D2: U25.14 (D2); also elsewhere on the board
D3: U25.15 (D3); also elsewhere on the board
D4: U25.16 (D4); also elsewhere on the board
D5: U25.17 (D5); also elsewhere on the board
D6: U25.18 (D6); also elsewhere on the board
D7: U25.19 (D7); also elsewhere on the board
EXT-RES: U25.4 (RESET); also elsewhere on the board
GND: J15.3, J16.3, NT1.1, U24.4, U24.7; also elsewhere on the board
INT_KM: U18.6; also elsewhere on the board
KBDCLK: J16.5, U25.1 (T0), U26.6; also elsewhere on the board
KBDDAT: J16.1, U25.27 (P10), U26.12; also elsewhere on the board
MSECLK: J15.5, U25.39 (T1), U26.4; also elsewhere on the board
MSEDAT: J15.1, U25.28 (P11), U26.2; also elsewhere on the board
unnamed: NT1.2, U25.2 (X1), U25.7 (EA), U25.20 (VSS)
unnamed: U25.23 (P22), U26.1
unnamed: U25.24 (P23), U26.3
unnamed: U18.4, U25.35 (P24/OB)
unnamed: U18.5, U25.36 (P25/BF)
unnamed: U25.37 (P26/DRQ), U26.5
unnamed: U25.38 (P27/DAK), U26.13
PROG: U25.25 (PROG); also elsewhere on the board
/CS_KB: U25.6 (CS); also elsewhere on the board
/RD: U25.8 (RD); also elsewhere on the board
/WR: U25.10 (WR); also elsewhere on the board

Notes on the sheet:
8 MHz Crystal Oscillator
NOTE: IMPORTANT KNOWN TO WORK: - VT82C42N (VIA) LIKELY TO WORK BUT UNTESTED: - HT6542B (Holtek) - 83C42 (Western Digital) - KBD42W11 (SMSC) KNOWN DO NOT WORK: - 8042 (Intel & clones of PC/AT era)
KEYBOARD AND MOUSE
